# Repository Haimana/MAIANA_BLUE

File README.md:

# MAIANA BLUE — Version 12 (MBv12)

Firmware and hardware design files for the MAIANA-class AIS transponder ecosystem. This project builds upon the open-source [MAIANA project](https://github.com/peterantypas/maiana) (GPL v3, Peter Antypas).

## Branch Context

The **`MBv12`** branch forms the foundation for **Version 12** of MAIANA Blue:
- Branch base: branched from **`cleanup/drop-legacy-bsp`** (inheriting firmware `FW 4.5.16` with N2K true heading support, GNSS autobaud, and consolidated `bsp_11_10` hardware support).
- Structure: streamlined workspace containing exclusively the active transponder firmware and the accompanying KiCad hardware design.

## Repository Layout

- **`Maiana_Blue_Ais_Firmware/`** — AIS transponder firmware configured for VS Code / PlatformIO (STM32L432 target).
- **`Maiana_Blue_Schematic/`** — KiCad project containing the complete schematic, PCB layout, and manufacturing files for MAIANA Blue v12.

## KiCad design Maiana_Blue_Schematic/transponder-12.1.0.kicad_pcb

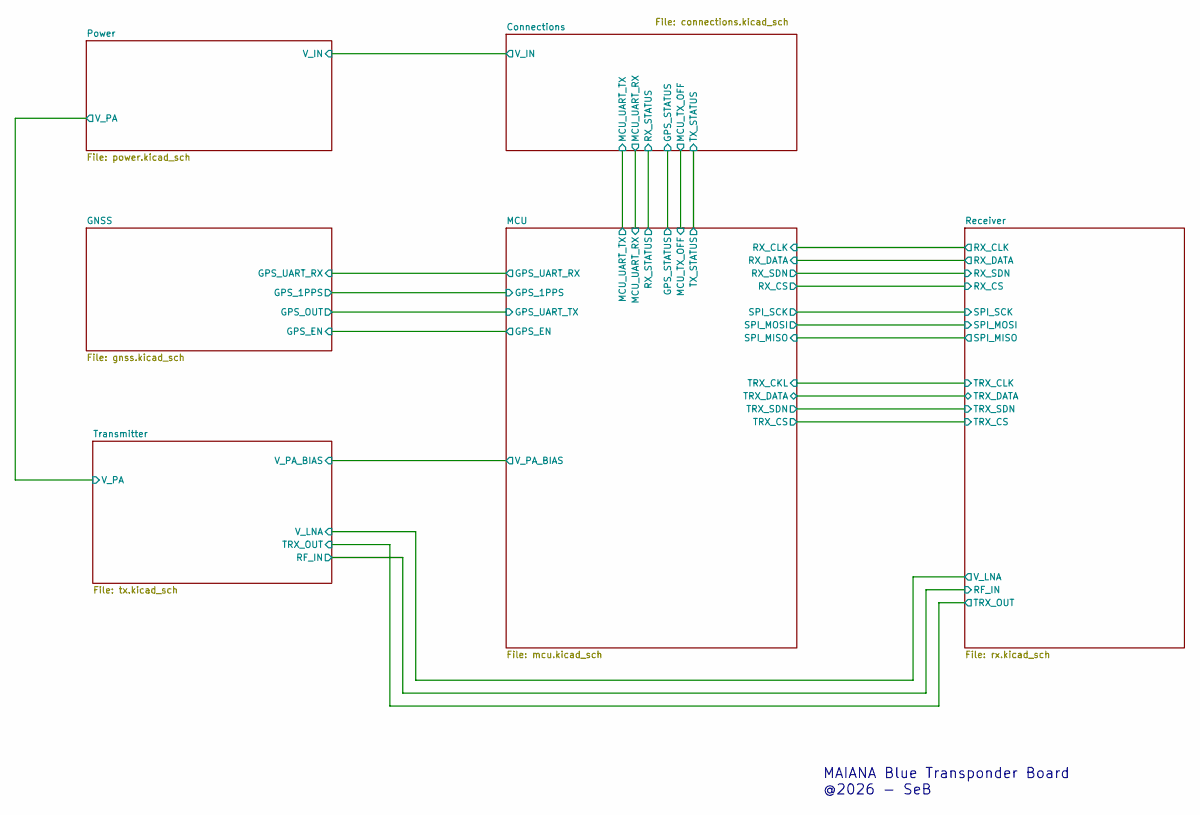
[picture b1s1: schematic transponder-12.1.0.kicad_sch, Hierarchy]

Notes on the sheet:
MAIANA Blue Transponder Board @2026 - SeB

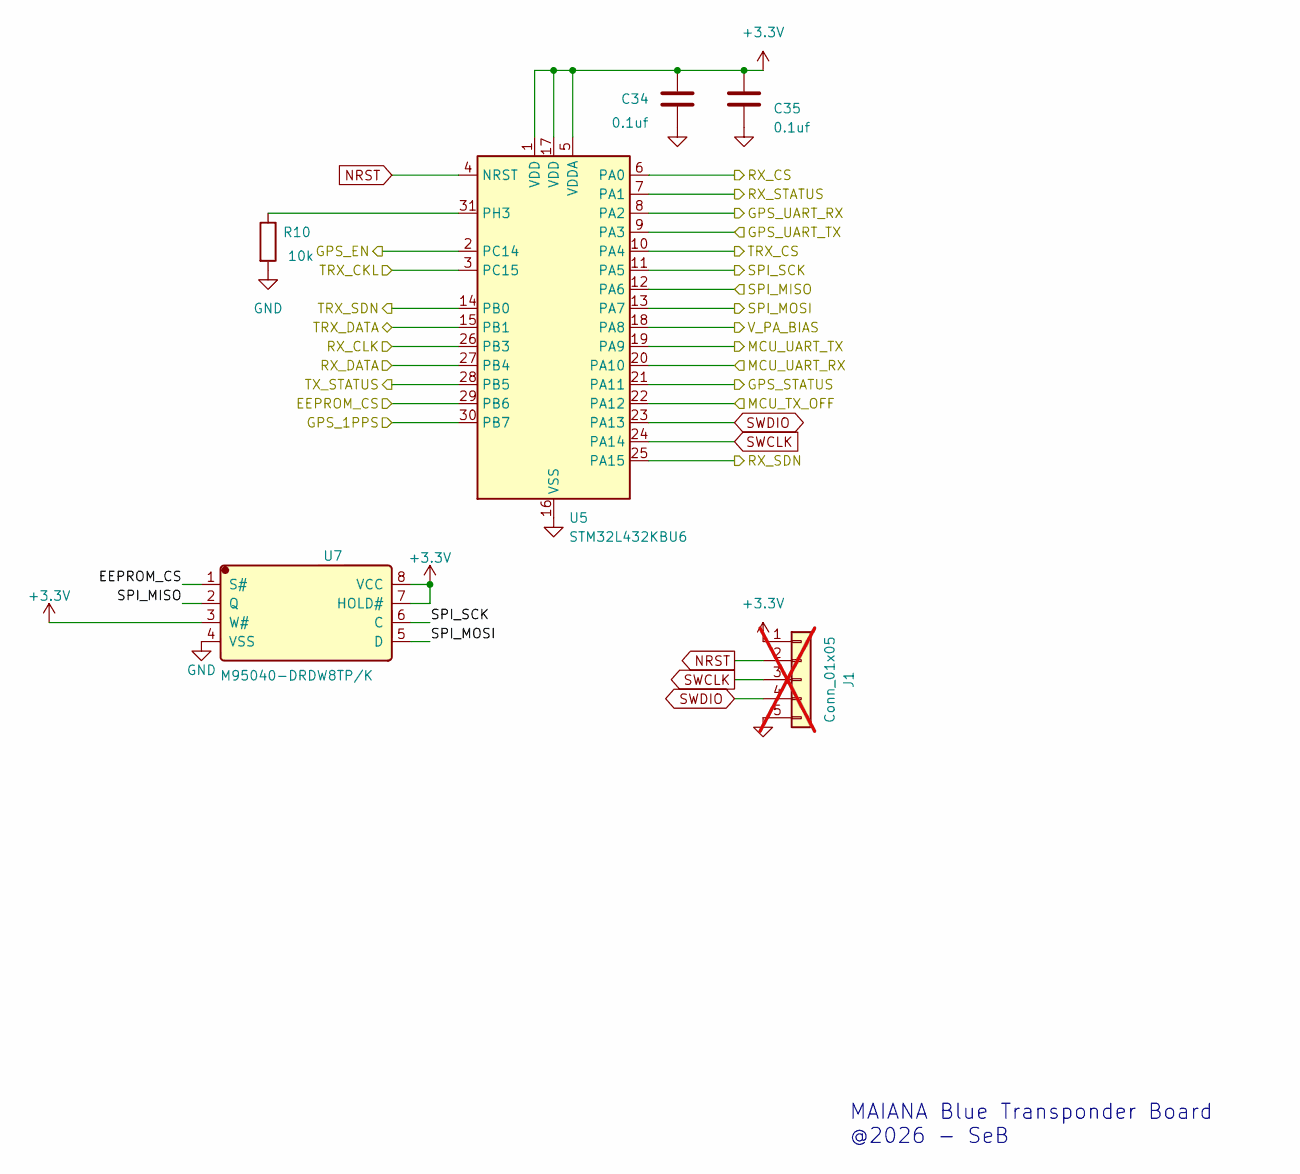
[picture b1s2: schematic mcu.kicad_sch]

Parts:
C34, C35: 0.1uf; C_0603_1608Metric
J1: Conn_01x05; PinHeader_1x05_P2.54mm_Vertical; not fitted
R10: 10k; R_0603_1608Metric
U5: STM32L432KBU6; QFN-32-1EP_5x5mm_P0.5mm_EP3.45x3.45mm; MPN STM32L432KBU6; LCSC C94784
U7: M95040-DRDW8TP/K; M95040-DRDW8TP_K; LCSC C2062181

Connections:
+3.3V: C34.2, C35.2, J1.1, U5.1 (VDD), U5.5 (VDDA), U5.17 (VDD), U7.3 (W#), U7.7 (HOLD#), U7.8 (VCC); also elsewhere on the board
/Connections/GPS_STATUS: U5.21 (PA11); also elsewhere on the board
/Connections/MCU_TX_OFF: U5.22 (PA12); also elsewhere on the board
/Connections/MCU_UART_RX: U5.20 (PA10); also elsewhere on the board
/Connections/MCU_UART_TX: U5.19 (PA9); also elsewhere on the board
/Connections/RX_STATUS: U5.7 (PA1); also elsewhere on the board
/Connections/TX_STATUS: U5.28 (PB5); also elsewhere on the board
/GNSS/GPS_1PPS: U5.30 (PB7); also elsewhere on the board
/GNSS/GPS_EN: U5.2 (PC14); also elsewhere on the board
/GNSS/GPS_OUT: U5.9 (PA3); also elsewhere on the board
/GNSS/GPS_UART_RX: U5.8 (PA2); also elsewhere on the board
/MCU/EEPROM_CS: U5.29 (PB6), U7.1 (S#)
/MCU/RX_CLK: U5.26 (PB3); also elsewhere on the board
/MCU/RX_CS: U5.6 (PA0); also elsewhere on the board
/MCU/RX_DATA: U5.27 (PB4); also elsewhere on the board
/MCU/RX_SDN: U5.25 (PA15); also elsewhere on the board
/MCU/SPI_MISO: U5.12 (PA6), U7.2 (Q); also elsewhere on the board
/MCU/SPI_MOSI: U5.13 (PA7), U7.5 (D); also elsewhere on the board
/MCU/SPI_SCK: U5.11 (PA5), U7.6 (C); also elsewhere on the board
/MCU/TRX_CKL: U5.3 (PC15); also elsewhere on the board
/MCU/TRX_CS: U5.10 (PA4); also elsewhere on the board
/MCU/TRX_DATA: U5.15 (PB1); also elsewhere on the board
/MCU/TRX_SDN: U5.14 (PB0); also elsewhere on the board
/MCU/V_PA_BIAS: U5.18 (PA8); also elsewhere on the board
GND: C34.1, C35.1, J1.5, R10.2, U5.16 (VSS), U5.32 (VSS), U5.33 (VSS), U7.4 (VSS); also elsewhere on the board
NRST: J1.2, U5.4 (NRST)
unnamed: R10.1, U5.31 (PH3)
SWCLK: J1.3, U5.24 (PA14)
SWDIO: J1.4, U5.23 (PA13)

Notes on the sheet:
MAIANA Blue Transponder Board @2026 - SeB

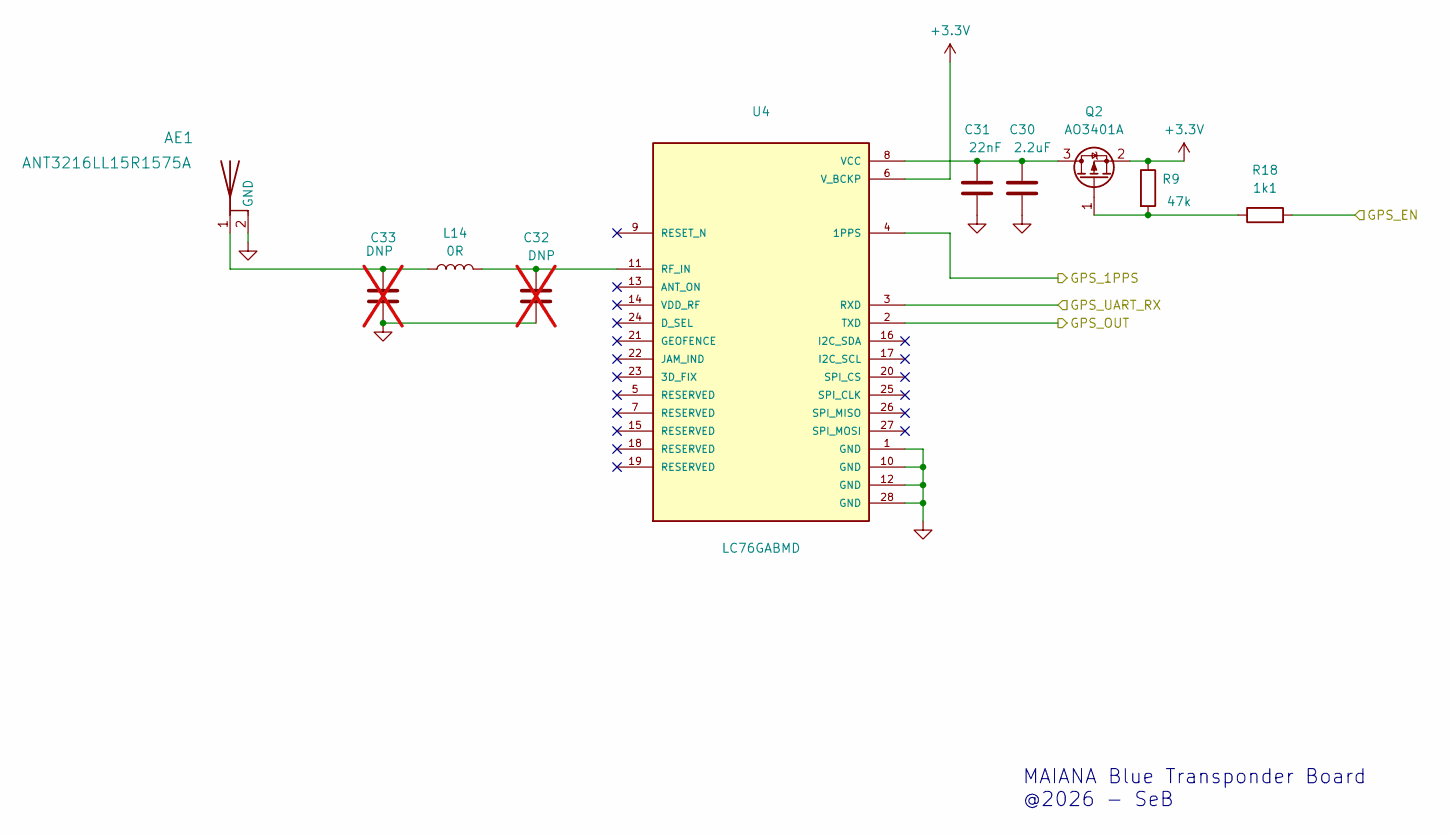
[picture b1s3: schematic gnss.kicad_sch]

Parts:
AE1: ANT3216LL15R1575A; MPN ANT3216LL15R1575A; LCSC C5561910
C30: 2.2uF; C_0603_1608Metric
C31: 22nF; C_0603_1608Metric
C32, C33: DNP; C_0603_1608Metric; not fitted
L14: 0R; L_0603_1608Metric
Q2: AO3401A; SOT-23
R9: 47k; R_0603_1608Metric
R18: 1k1; R_0603_1608Metric
U4: LC76GABMD; MPN LC76GABMD; LCSC C7437114

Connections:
+3.3V: Q2.2 (S), R9.1, U4.6 (V_BCKP); also elsewhere on the board
/GNSS/GPS_1PPS: U4.4 (1PPS); also elsewhere on the board
/GNSS/GPS_EN: R18.2; also elsewhere on the board
/GNSS/GPS_OUT: U4.2 (TXD); also elsewhere on the board
/GNSS/GPS_UART_RX: U4.3 (RXD); also elsewhere on the board
GND: AE1.2 (GND_2), C30.1, C31.1, C32.1, C33.1, U4.1 (GND), U4.10 (GND), U4.12 (GND), U4.28 (GND); also elsewhere on the board
unnamed: AE1.1, C33.2, L14.1
unnamed: C30.2, C31.2, Q2.3 (D), U4.8 (VCC)
unnamed: Q2.1 (G), R9.2, R18.1
unnamed: C32.2, L14.2, U4.11 (RF_IN)

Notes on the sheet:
MAIANA Blue Transponder Board @2026 - SeB

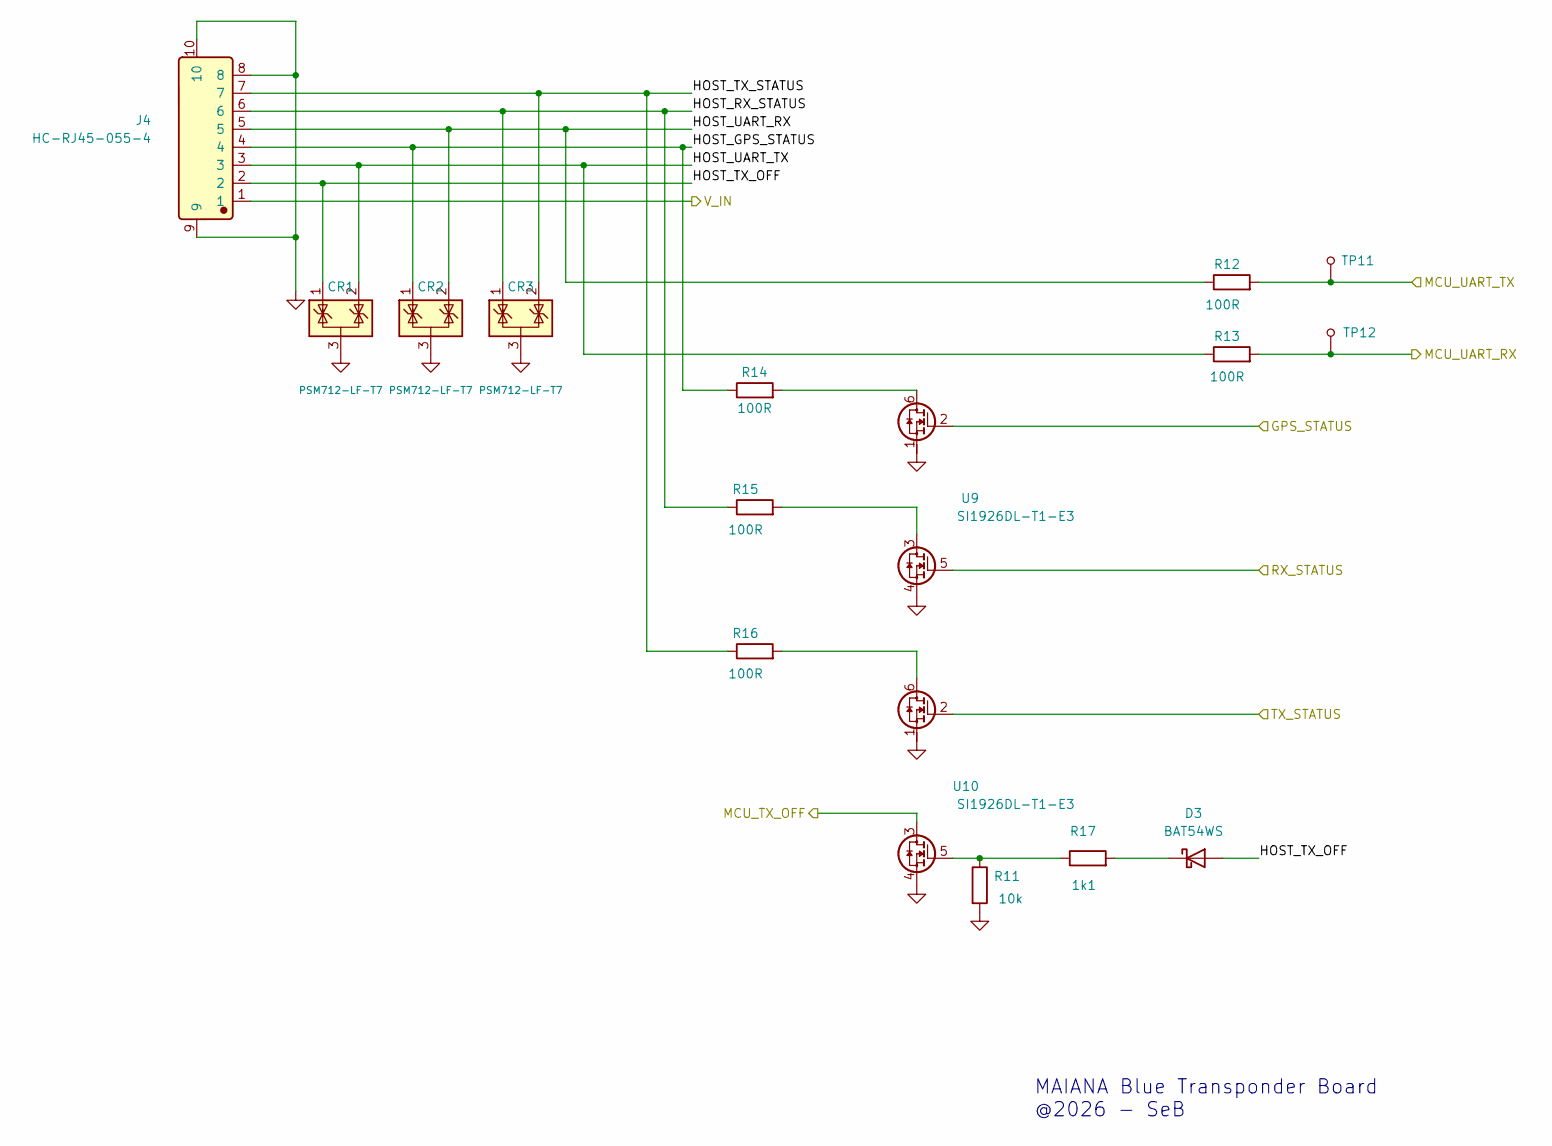
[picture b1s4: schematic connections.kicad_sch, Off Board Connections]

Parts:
CR1, CR2, CR3: PSM712-LF-T7; SOT-23; Manufacturer Part PSM712-LF-T7; LCSC C32677
D3: BAT54WS; D_SOD-323; Manufacturer Part BAT54WS; LCSC C22629
J4: HC-RJ45-055-4; Manufacturer Part HC-RJ45-055-4; LCSC C3000211
R11: 10k; R_0603_1608Metric
R12, R13, R14, R15, R16: 100R; R_0603_1608Metric
R17: 1k1; R_0603_1608Metric
TP11, TP12: TP_1.2MM
U9, U10: SI1926DL-T1-E3; SOT-363_SC-70-6

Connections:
/Connections/GPS_STATUS: U9.2 (G1); also elsewhere on the board
/Connections/HOST_GPS_STATUS: CR2.1, J4.4, R14.1
/Connections/HOST_RX_STATUS: CR3.1, J4.6, R15.1
/Connections/HOST_TX_OFF: CR1.1, D3.2 (A), J4.2
/Connections/HOST_TX_STATUS: CR3.2, J4.7, R16.1
/Connections/HOST_UART_RX: CR2.2, J4.5, R12.1
/Connections/HOST_UART_TX: CR1.2, J4.3, R13.1
/Connections/MCU_TX_OFF: U10.3 (D2); also elsewhere on the board
/Connections/MCU_UART_RX: R13.2, TP12.1 (P_1); also elsewhere on the board
/Connections/MCU_UART_TX: R12.2, TP11.1 (P_1); also elsewhere on the board
/Connections/RX_STATUS: U9.5 (G2); also elsewhere on the board
/Connections/TX_STATUS: U10.2 (G1); also elsewhere on the board
/Connections/V_IN: J4.1; also elsewhere on the board
GND: CR1.3 (GND), CR2.3 (GND), CR3.3 (GND), J4.8, J4.9, J4.10, R11.2, U9.1 (S1), U9.4 (S2), U10.1 (S1), U10.4 (S2); also elsewhere on the board
unnamed: D3.1 (K), R17.2
unnamed: R14.2, U9.6 (D1)
unnamed: R15.2, U9.3 (D2)
unnamed: R16.2, U10.6 (D1)
unnamed: R11.1, R17.1, U10.5 (G2)

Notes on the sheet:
MAIANA Blue Transponder Board @2026 - SeB

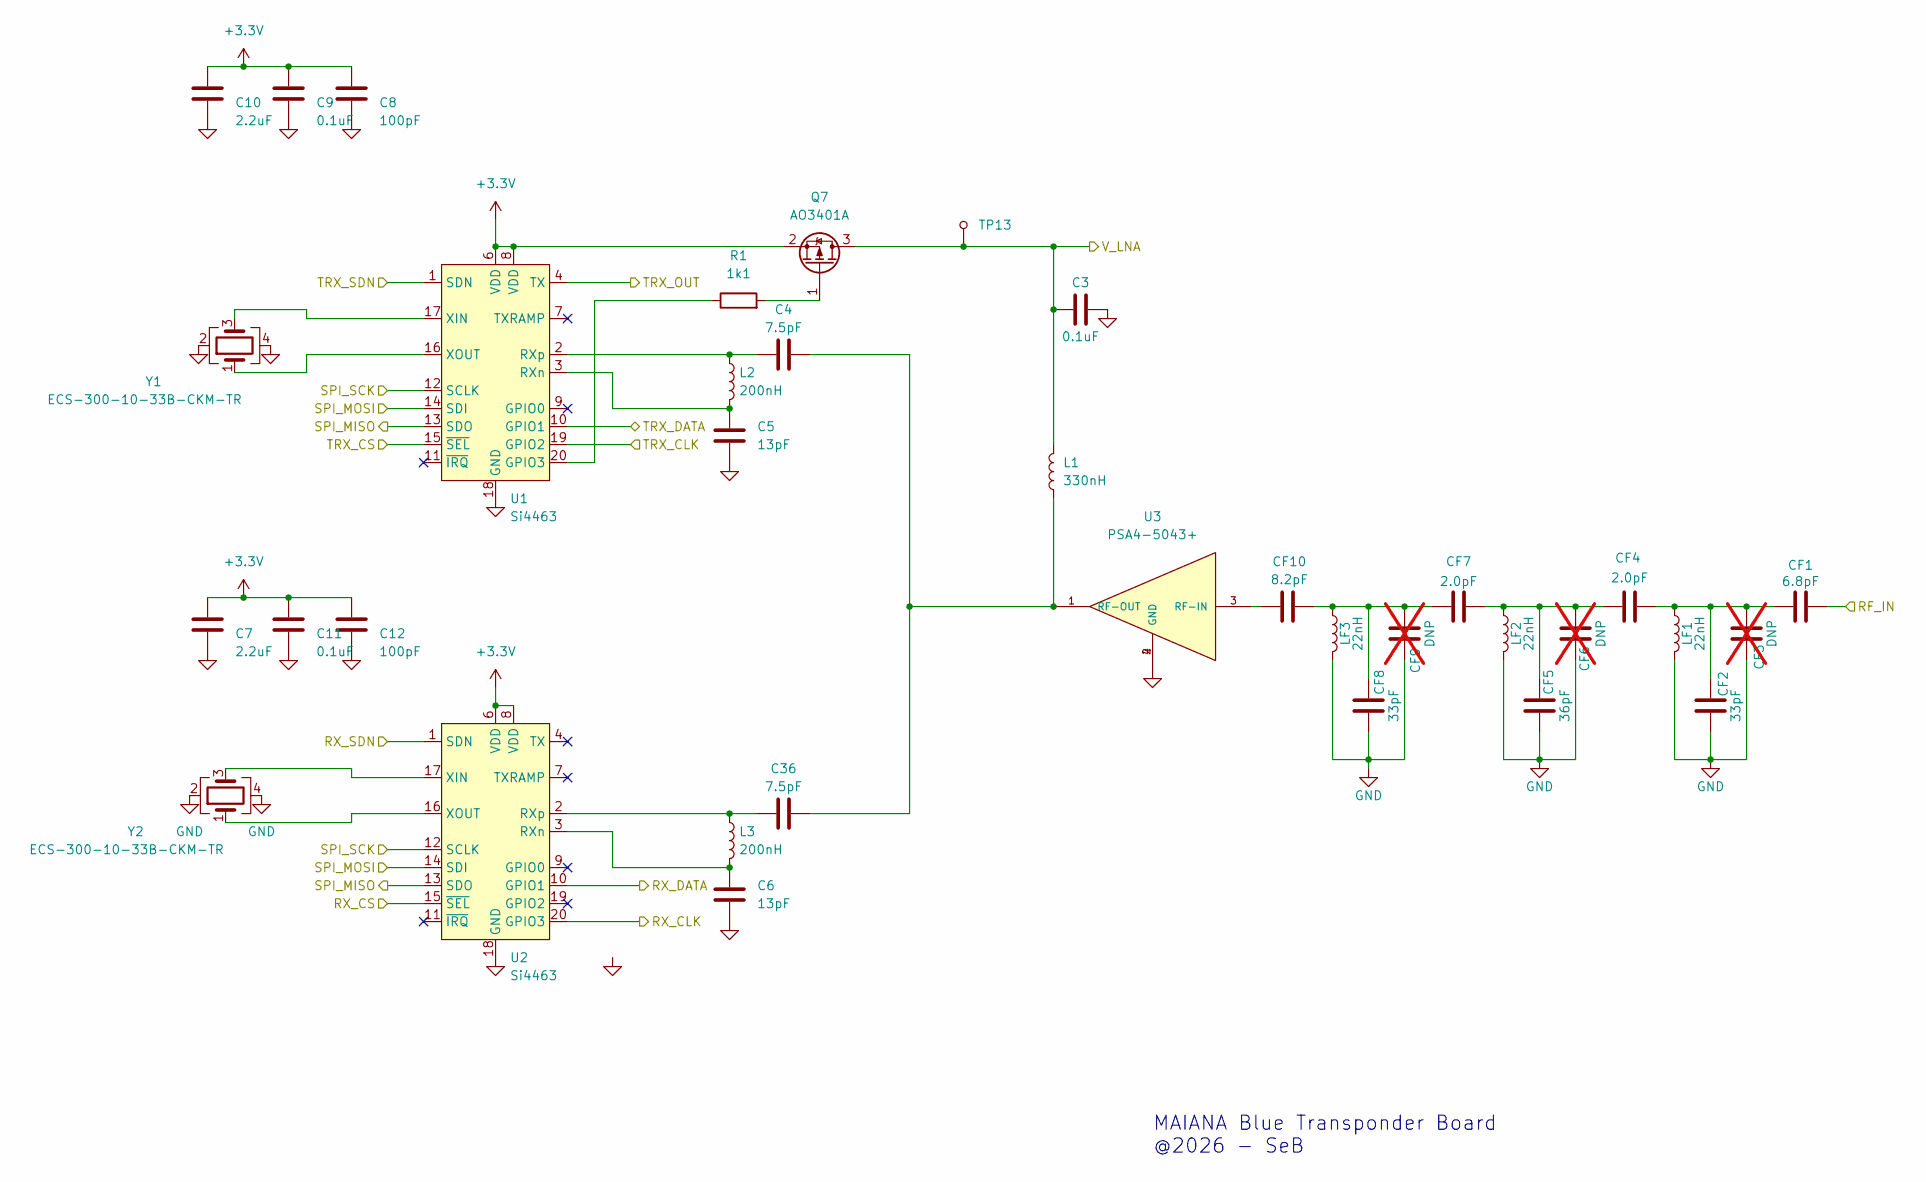
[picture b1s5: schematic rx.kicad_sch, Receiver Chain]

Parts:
C3, C9, C11: 0.1uF; C_0603_1608Metric
C4, C36: 7.5pF; C_0402_1005Metric
C5, C6: 13pF; C_0402_1005Metric
C7, C10: 2.2uF; C_0603_1608Metric
C8, C12: 100pF; C_0603_1608Metric
CF1: 6.8pF; C_0603_1608Metric; Tolerance ±0.1pF; MPN GRM1885C1H6R8BA01D; LCSC C162244
CF2, CF8: 33pF; C_0603_1608Metric; Tolerance ±2%; MPN GRM1885C1H330GA01D; LCSC C426330
CF3, CF6, CF9: DNP; C_0603_1608Metric; MPN DNP; not fitted
CF4, CF7: 2.0pF; C_0603_1608Metric; Tolerance ±0.1pF; MPN GRM1885C1H2R0BA01D; LCSC C81437
CF5: 36pF; C_0603_1608Metric; Tolerance ±2%; MPN CC0603GRNPO9BN360; LCSC C519462
CF10: 8.2pF; C_0603_1608Metric; Tolerance ±0.1pF; MPN GRM1885C1H8R2BA01D; LCSC C162252
L1: 330nH; L_0603_1608Metric; Manufacturer Part LQW18ANR33G80D; LCSC C440245
L2, L3: 200nH; L_0402_1005Metric
LF1, LF2, LF3: 22nH; L_0603_1608Metric; Tolerance ±2%; MPN LQW18AN22NG00D; LCSC C84341
Q7: AO3401A; SOT-23
R1: 1k1; R_0603_1608Metric
TP13: TP_1.2MM
U1, U2: Si4463; QFN-20-1EP_4x4mm_P0.5mm_EP2.6x2.6mm_ThermalVias; MPN SI4463-C2A-GMR; LCSC C476202
U3: PSA4-5043+; PSA4-5043_
Y1, Y2: ECS-300-10-33B-CKM-TR; Crystal_SMD_3225-4Pin_3.2x2.5mm

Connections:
+3.3V: C7.2, C8.2, C9.2, C10.2, C11.2, C12.2, Q7.2 (S), U1.6 (VDD), U1.8 (VDD), U2.6 (VDD), U2.8 (VDD); also elsewhere on the board
/MCU/RX_CLK: U2.20 (GPIO3); also elsewhere on the board
/MCU/RX_CS: U2.15 (~SEL); also elsewhere on the board
/MCU/RX_DATA: U2.10 (GPIO1); also elsewhere on the board
/MCU/RX_SDN: U2.1 (SDN); also elsewhere on the board
/MCU/SPI_MISO: U1.13 (SDO), U2.13 (SDO); also elsewhere on the board
/MCU/SPI_MOSI: U1.14 (SDI), U2.14 (SDI); also elsewhere on the board
/MCU/SPI_SCK: U1.12 (SCLK), U2.12 (SCLK); also elsewhere on the board
/MCU/TRX_CKL: U1.19 (GPIO2); also elsewhere on the board
/MCU/TRX_CS: U1.15 (~SEL); also elsewhere on the board
/MCU/TRX_DATA: U1.10 (GPIO1); also elsewhere on the board
/MCU/TRX_SDN: U1.1 (SDN); also elsewhere on the board
/Receiver/RF_IN: CF1.2; also elsewhere on the board
/Receiver/TRX_OUT: U1.4 (TX); also elsewhere on the board
/Receiver/V_LNA: C3.1, L1.2, Q7.3 (D), TP13.1; also elsewhere on the board
GND: C3.2, C5.2, C6.2, C7.1, C8.1, C9.1, C10.1, C11.1, C12.1, CF2.2, CF3.2, CF5.2, CF6.2, CF8.2, CF9.2, LF1.2, LF2.2, LF3.2, U1.18 (GND), U1.21 (GND), U2.18 (GND), U2.21 (GND), U3.2 (GND), U3.4 (GND), Y1.2, Y1.4, Y2.2, Y2.4; also elsewhere on the board
unnamed: CF1.1, CF2.1, CF3.1, CF4.2, LF1.1
unnamed: CF4.1, CF5.1, CF6.1, CF7.2, LF2.1
unnamed: CF7.1, CF8.1, CF9.1, CF10.2, LF3.1
unnamed: Q7.1 (G), R1.2
unnamed: R1.1, U1.20 (GPIO3)
unnamed: C5.1, L2.2, U1.3 (RXn)
unnamed: C4.1, L2.1, U1.2 (RXp)
unnamed: U1.17 (XIN), Y1.3
unnamed: U1.16 (XOUT), Y1.1
unnamed: C6.1, L3.2, U2.3 (RXn)
unnamed: C36.1, L3.1, U2.2 (RXp)
unnamed: U2.17 (XIN), Y2.3
unnamed: U2.16 (XOUT), Y2.1
unnamed: CF10.1, U3.3 (RF-IN)
unnamed: C4.2, C36.2, L1.1, U3.1 (RF-OUT)

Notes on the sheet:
MAIANA Blue Transponder Board @2026 - SeB

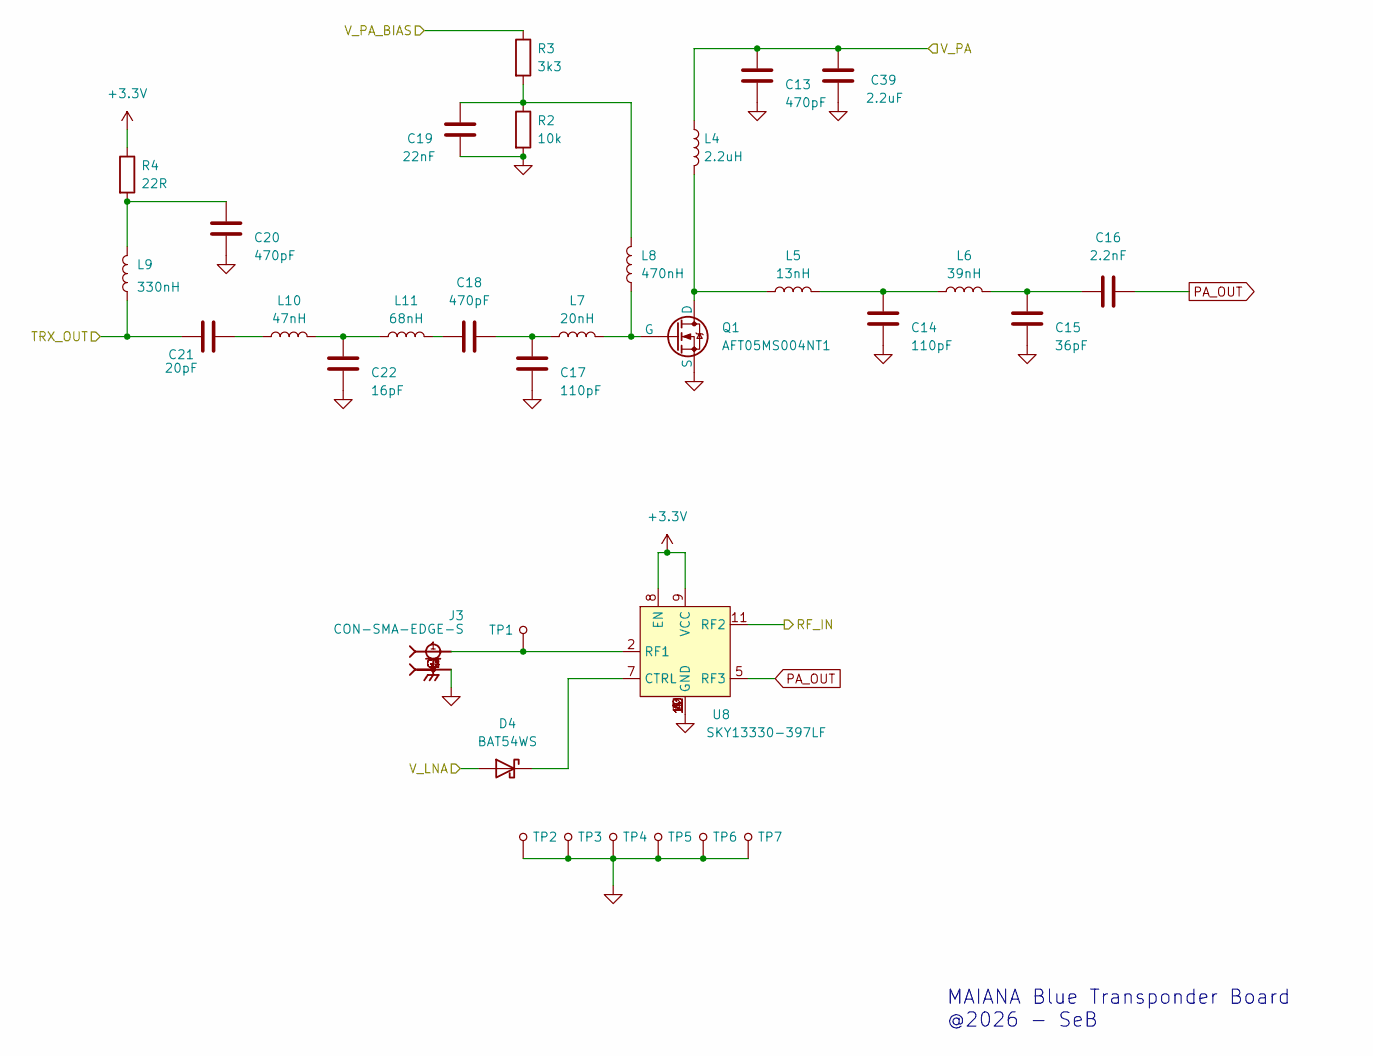
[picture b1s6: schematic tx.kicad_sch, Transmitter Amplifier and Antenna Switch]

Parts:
C13, C18, C20: 470pF; C_0603_1608Metric
C14, C17: 110pF; C_0603_1608Metric
C15: 36pF; C_0603_1608Metric
C16: 2.2nF; C_0603_1608Metric
C19: 22nF; C_0603_1608Metric
C21: 20pF; C_0603_1608Metric
C22: 16pF; C_0603_1608Metric
C39: 2.2uF; C_0603_1608Metric
D4: BAT54WS; D_SOD-323; Manufacturer Part BAT54WS; LCSC C22629
J3: CON-SMA-EDGE-S; RFSOLUTIONS_CON-SMA-EDGE-S; PARTREV 1; DigiKey_Part_Number CON-SMA-EDGE-S-ND
L4: 2.2uH; L_0603_1608Metric
L5: 13nH; L_0603_1608Metric
L6: 39nH; L_0603_1608Metric
L7: 20nH; L_0603_1608Metric
L8: 470nH; L_0603_1608Metric
L9: 330nH; L_0603_1608Metric; Manufacturer Part LQW18ANR33G80D; LCSC C440245
L10: 47nH; L_0603_1608Metric
L11: 68nH; L_0603_1608Metric
Q1: AFT05MS004NT1; SOT-89-3
R2: 10k; R_0603_1608Metric
R3: 3k3; R_0603_1608Metric
R4: 22R; R_0603_1608Metric
TP1: TP_1.0MM
TP2, TP3, TP4, TP5, TP6, TP7: TP_1.2MM
U8: SKY13330-397LF; QFN50P200X200X65-13N

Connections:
+3.3V: R4.1, U8.8 (EN), U8.9 (VCC); also elsewhere on the board
/MCU/V_PA_BIAS: R3.1; also elsewhere on the board
/Power/V_PA: C13.2, C39.2, L4.1; also elsewhere on the board
/Receiver/RF_IN: U8.11 (RF2); also elsewhere on the board
/Receiver/TRX_OUT: C21.1, L9.1; also elsewhere on the board
/Receiver/V_LNA: D4.2 (A); also elsewhere on the board
GND: C13.1, C14.1, C15.1, C17.1, C19.1, C20.1, C22.1, C39.1, J3.G1, J3.G2, J3.G3, J3.G4, Q1.2 (S), R2.2, TP2.1 (P_1), TP3.1 (P_1), TP4.1 (P_1), TP5.1 (P_1), TP6.1 (P_1), TP7.1 (P_1), U8.1 (GND), U8.3 (GND), U8.4 (GND), U8.6 (GND), U8.10 (GND), U8.12 (GND), U8.13 (GND); also elsewhere on the board
unnamed: C14.2, L5.2, L6.1
unnamed: C15.2, C16.1, L6.2
unnamed: C17.2, C18.2, L7.1
unnamed: C18.1, L11.2
unnamed: C19.2, L8.2, R2.1, R3.2
unnamed: C20.2, L9.2, R4.2
unnamed: C21.2, L10.1
unnamed: C22.2, L10.2, L11.1
unnamed: D4.1 (K), U8.7 (CTRL)
unnamed: L4.2, L5.1, Q1.3 (D)
unnamed: L7.2, L8.1, Q1.1 (G)
unnamed: J3.1, TP1.1 (P_1), U8.2 (RF1)
PA_OUT: C16.2, U8.5 (RF3)

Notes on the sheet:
MAIANA Blue Transponder Board @2026 - SeB

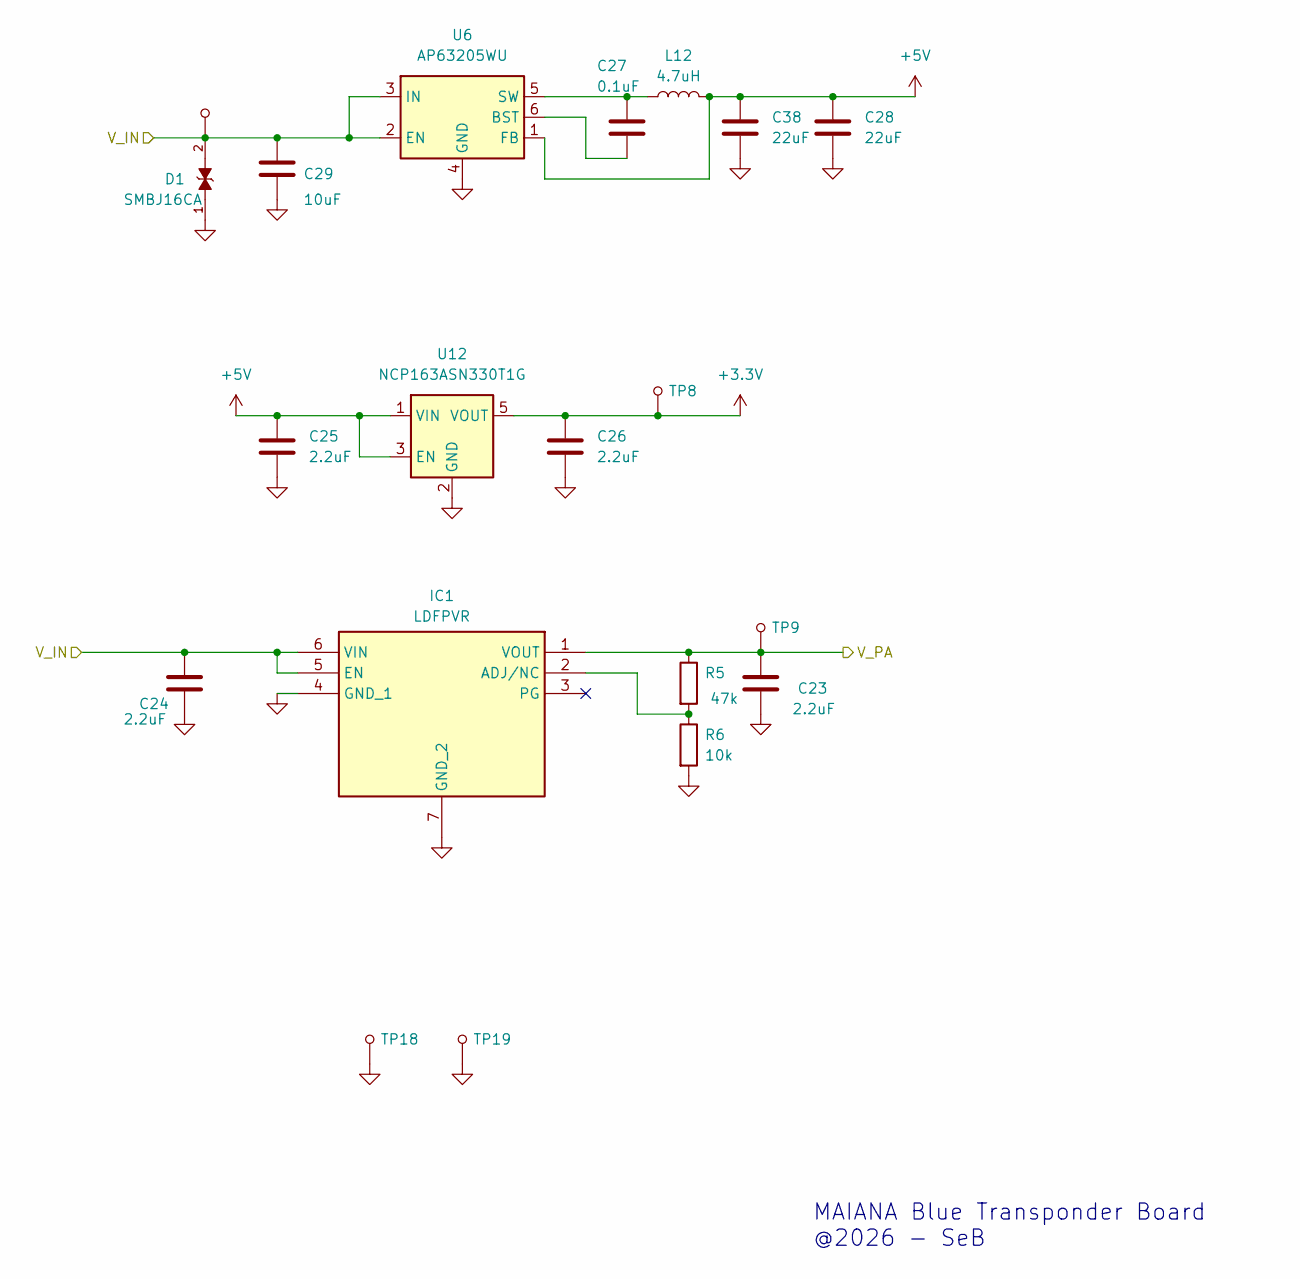
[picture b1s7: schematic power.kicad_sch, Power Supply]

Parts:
C23, C24, C25, C26: 2.2uF; C_0603_1608Metric
C27: 0.1uF; C_0603_1608Metric
C28, C38: 22uF; C_0805_2012Metric
C29: 10uF; C_0805_2012Metric
D1: SMBJ16CA; DIOM4336X265N; PARTREV I2102; LCSC C113990
IC1: LDFPVR; SON65P200X200X100-7N-D; Mouser Part Number 511-LDFPVR
L12: 4.7uH; L_1210_3225Metric; Manufacturer Part DFE322512F-4R7M=P2; LCSC C703083
R5: 47k; R_0603_1608Metric
R6: 10k; R_0603_1608Metric
TP8, TP9, TP10, TP18, TP19: TP_1.2MM
U6: AP63205WU; TSOT-23-6
U12: NCP163ASN330T1G; SOT-23-5

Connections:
+3.3V: C26.1, TP8.1 (P_1), U12.5 (VOUT); also elsewhere on the board
+5V: C25.1, C28.1, C38.1, L12.2, U6.1 (FB), U12.1 (VIN), U12.3 (EN)
/Connections/V_IN: C24.2, C29.1, D1.2, IC1.5 (EN), IC1.6 (VIN), TP10.1 (P_1), U6.2 (EN), U6.3 (IN); also elsewhere on the board
/Power/V_PA: C23.2, IC1.1 (VOUT), R5.1, TP9.1; also elsewhere on the board
GND: C23.1, C24.1, C25.2, C26.2, C28.2, C29.2, C38.2, D1.1, IC1.4 (GND_1), IC1.7 (GND_2), R6.2, TP18.1 (P_1), TP19.1 (P_1), U6.4 (GND), U12.2 (GND); also elsewhere on the board
unnamed: IC1.2 (ADJ/NC), R5.2, R6.1
unnamed: C27.1, U6.6 (BST)
unnamed: C27.2, L12.1, U6.5 (SW)

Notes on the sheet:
MAIANA Blue Transponder Board @2026 - SeB

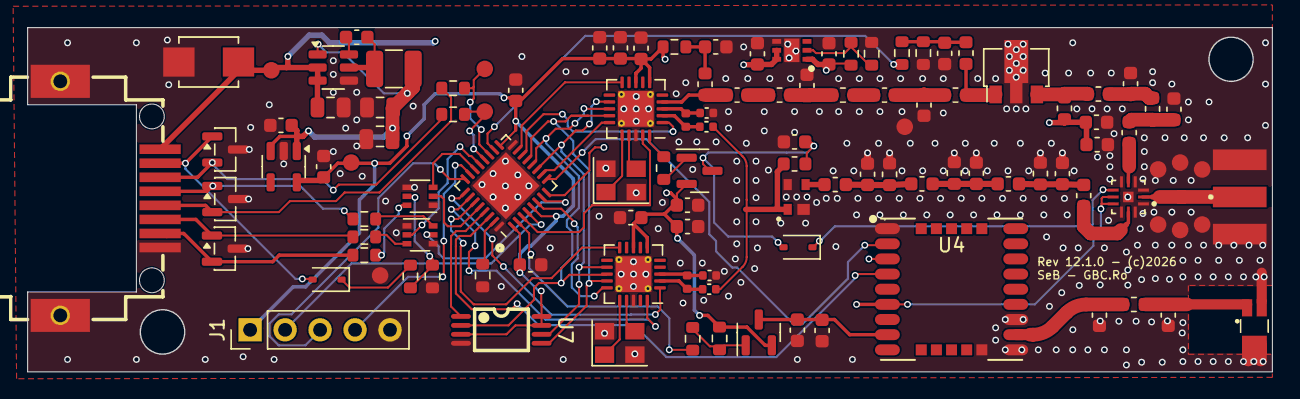
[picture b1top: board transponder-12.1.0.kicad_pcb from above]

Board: 4 copper layers, 90.4 x 25.0 mm, 115 parts (0 on the bottom side), 81 nets.

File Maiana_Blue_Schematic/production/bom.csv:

Designator,Footprint,Quantity,Value,LCSC Part #
AE1,ANT3216LL15R1575A,1,ANT3216LL15R1575A,C5561910
"C10, C23, C24, C25, C26, C30, C39, C7",0603,8,2.2uF,C23630
"C11, C27, C3, C34, C35, C9",0603,6,0.1uF,C14663
"C12, C8",0603,2,100pF,C14665
"C13, C18, C20",0603,3,470pF,C106211
"C14, C17",0603,2,110pF,C327208
C15,0603,1,36pF,C134070
C16,0603,1,2.2nF,C1604
"C19, C31",0603,2,22nF,C57112
C21,0603,1,20pF,C105621
C22,0603,1,16pF,C327125
"C28, C38",0805,2,22uF,C45783
C29,0805,1,10uF,C15850
"C36, C4",0402,2,7.5pF,C43514
"C5, C6",0402,2,13pF,C130119
CF1,0603,1,6.8pF,C162244
CF10,0603,1,8.2pF,C162252
"CF2, CF8",0603,2,33pF,C426330
"CF4, CF7",0603,2,2.0pF,C81437
CF5,0603,1,36pF,C519462
"CR1, CR2, CR3",SOT-23,3,PSM712-LF-T7,C32677
D1,DIOM4336X265N,1,SMBJ16CA,C113990
"D3, D4",D_SOD-323,2,BAT54WS,C22629
IC1,SON65P200X200X100-7N-D,1,LDFPVR,C2969978
J3,RFSOLUTIONS_CON-SMA-EDGE-S,1,CON-SMA-EDGE-S,C5723200
J4,HC-RJ45-055-4,1,HC-RJ45-055-4,C3000211
"L1, L9",0603,2,330nH,C440245
L10,0603,1,47nH,C524644
L11,0603,1,68nH,C86135
L12,1210,1,4.7uH,C703083
L14,0603,1,0R,C21189
"L2, L3",0402,2,200nH,C2045944
L4,0603,1,2.2uH,C285966
L5,0603,1,13nH,C5752381
L6,0603,1,39nH,C2042966
L7,0603,1,20nH,C77124
L8,0603,1,470nH,C98097
"LF1, LF2, LF3",0603,3,22nH,C84341
Q1,SOT-89-3,1,AFT05MS004NT1,C713822
"Q2, Q7",SOT-23,2,AO3401A,C15127
"R1, R17, R18",0603,3,1k1,C2906975
"R10, R11, R2, R6",0603,4,10k,C25804
"R12, R13, R14, R15, R16",0603,5,100R,C22775
R3,0603,1,3k3,C22978
R4,0603,1,22R,C23345
"R5, R9",0603,2,47k,C25819
TP1,TP_1.0MM,1,~,
"TP10, TP11, TP12, TP18, TP19, TP2, TP3, TP4, TP5, TP6, TP7, TP8",TP_1.2MM,12,~,
"U1, U2",QFN-20-1EP_4x4mm_P0.5mm_EP2.6x2.6mm_ThermalVias,2,Si4463,C476202
"U10, U9",SOT-363_SC-70-6,2,SI1926DL-T1-E3,C5190214
U12,SOT-23-5,1,NCP163ASN330T1G,C603656
U3,PSA4-5043_,1,PSA4-5043+,C5240848
U4,LC76GABMD,1,LC76GABMD,C7437114
U5,QFN-32-1EP_5x5mm_P0.5mm_EP3.45x3.45mm,1,STM32L432KBU6,C94784
U6,TSOT-23-6,1,AP63205WU,C2071056
U7,M95040-DRDW8TP_K,1,M95040-DRDW8TP/K,C2062181
U8,QFN50P200X200X65-13N,1,SKY13330-397LF,C2654715
"Y1, Y2",Crystal_SMD_3225-4Pin_3.2x2.5mm,2,ECS-300-10-33B-CKM-TR,C19711725

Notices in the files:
Maiana_Blue_Ais_Firmware/Src/bsp/bsp_12_1.cpp:
Copyright (c) 2016-2020 Peter Antypas
The firmware is free software: you can redistribute it and/or modify
it under the terms of the GNU General Public License as published by
the Free Software Foundation, either version 3 of the License, or
(at your option) any later version.
Maiana_Blue_11.9.2/connections.kicad_sch:
(c) 2016-2024 Maverick Labs LLC
Maiana_Blue_N2000_v8.2/Maiana_Blue_N2000_v8.2.kicad_pcb:
(c)2025 GBC.ro
Maiana_Blue_Schematic/transponder-12.1.0.kicad_pcb:
Rev 12.1.0 - (c)2026
